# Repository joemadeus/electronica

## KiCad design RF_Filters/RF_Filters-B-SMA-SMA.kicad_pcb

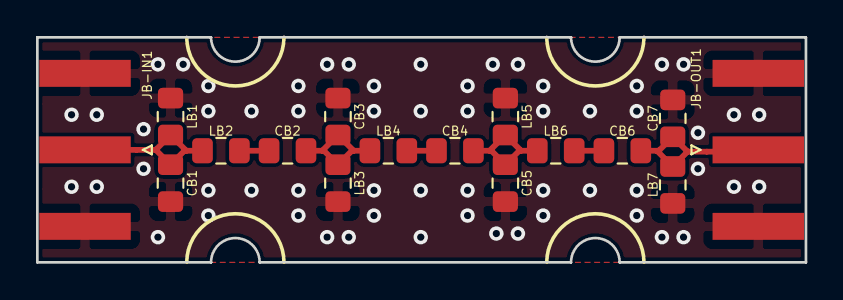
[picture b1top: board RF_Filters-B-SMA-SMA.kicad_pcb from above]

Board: 2 copper layers, 42.7 x 12.5 mm, 16 parts (0 on the bottom side), 8 nets.

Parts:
CB1, CB2, CB3, CB4, CB5, CB6, CB7: C; C_0805_2012Metric_Pad1.15x1.40mm_HandSolder
JB-IN1: Conn_Coaxial; SMA_Amphenol_132289_EdgeMount
JB-OUT1: Conn_Coaxial; SMA_Amphenol_132289_EdgeMount
LB1, LB2, LB3, LB4, LB5, LB6, LB7: L; L_0805_2012Metric_Pad1.15x1.40mm_HandSolder

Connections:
GND: CB1.2, CB3.2, CB5.2, CB7.2, JB-IN1.2, JB-OUT1.2, LB1.2, LB3.2, LB5.2, LB7.2
unnamed: CB1.1, JB-IN1.1, LB1.1, LB2.1
unnamed: CB2.1, CB3.1, LB3.1, LB4.1
unnamed: CB2.2, LB2.2
unnamed: CB4.1, CB5.1, LB5.1, LB6.1
unnamed: CB4.2, LB4.2
unnamed: CB6.1, CB7.1, JB-OUT1.1, LB7.1
unnamed: CB6.2, LB6.2

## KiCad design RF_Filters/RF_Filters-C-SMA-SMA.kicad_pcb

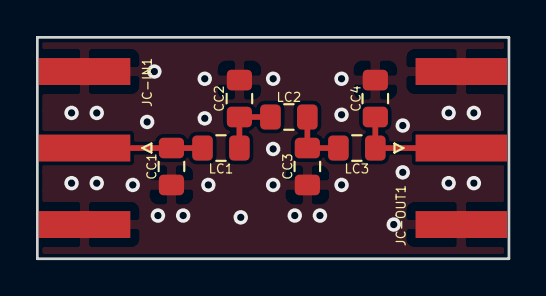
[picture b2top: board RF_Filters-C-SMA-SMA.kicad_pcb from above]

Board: 2 copper layers, 26.2 x 12.3 mm, 9 parts (0 on the bottom side), 5 nets.

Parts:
CC1, CC2, CC3, CC4: C; C_0805_2012Metric_Pad1.15x1.40mm_HandSolder
JC-IN1: Conn_Coaxial; SMA_Amphenol_132289_EdgeMount
JC-OUT1: Conn_Coaxial; SMA_Amphenol_132289_EdgeMount
LC1, LC2, LC3: L; L_0805_2012Metric_Pad1.15x1.40mm_HandSolder

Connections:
GND: CC1.2, CC2.2, CC3.2, CC4.2, JC-IN1.2, JC-OUT1.2
unnamed: CC1.1, JC-IN1.1, LC1.1
unnamed: CC2.1, LC1.2, LC2.1
unnamed: CC3.1, LC2.2, LC3.1
unnamed: CC4.1, JC-OUT1.1, LC3.2
